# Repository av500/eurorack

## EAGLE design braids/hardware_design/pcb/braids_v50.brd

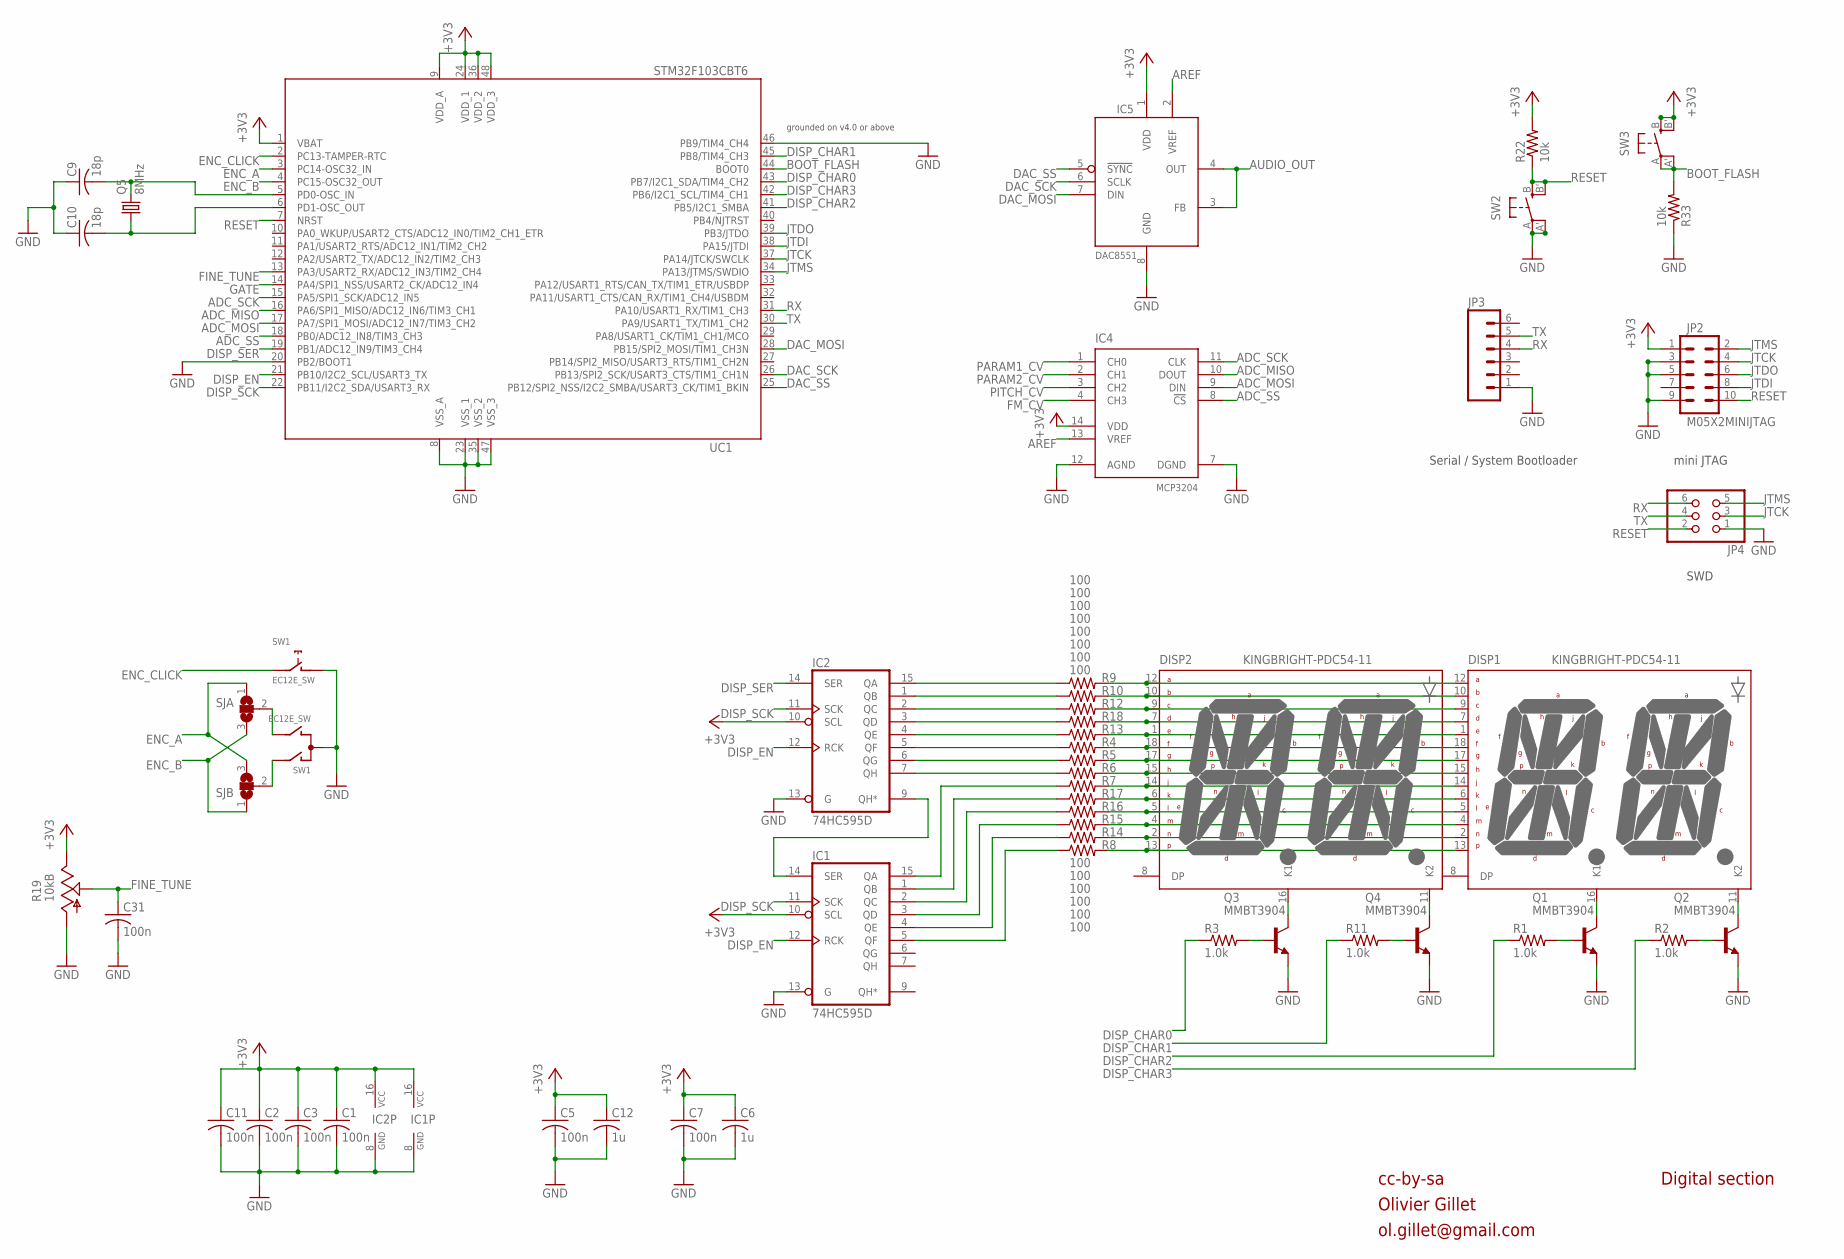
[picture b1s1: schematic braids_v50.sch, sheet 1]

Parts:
C1, C2, C3, C5, C7, C11, C31: 100n; C0603
C6, C12: 1u; C0603
C9, C10: 18p; C0603
DISP1, DISP2: KINGBRIGHT-PDC54-11; PDC54
IC1, IC2: 74HC595D; SO16
IC4: MCP3204; SO14
IC5: DAC8551; MSOP-8
JP2: M05X2MINIJTAG; 2X5-1.27
JP3: M06SIP; 1X06
JP4: PINHD-2X3"; 2X03
Q1, Q2, Q3, Q4: MMBT3904; SOT23-BEC
Q5: 8MHz; HC49UP
R1, R2, R3, R11: 1.0k; R0603
R4, R5, R6, R7, R8, R9, R10, R12, R13, R14, R15, R16, R17, R18: 100; R0603
R19: 10kB; ALPS_POT_VERTICAL_PS
R22, R33: 10k; R0603
SJA: SJ2W; SJ_2
SJB: SJ2W; SJ_2
SW1: EC12E_SW; ALPS_EC12E_SW
SW2, SW3: EVQQ2; EVQ-Q2
UC1: STM32F103CBT6; LQFP48

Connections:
+3V3: C1.1, C2.1, C3.1, C5.1, C6.1, C7.1, C11.1, C12.1, IC1.10 (SCL), IC1.16 (VCC), IC2.10 (SCL), IC2.16 (VCC), IC4.14 (VDD), IC5.1 (VDD), JP2.1, R19.P$1 (E), R22.2, SW3.B (S), SW3.B' (S1), UC1.1 (VBAT), UC1.9 (VDD_A), UC1.24 (VDD_1), UC1.36 (VDD_2), UC1.48 (VDD_3); also elsewhere on the board
ADC_MISO: IC4.10 (DOUT), UC1.16 (PA6/SPI1_MISO/ADC12_IN6/TIM3_CH1)
ADC_MOSI: IC4.9 (DIN), UC1.17 (PA7/SPI1_MOSI/ADC12_IN7/TIM3_CH2)
ADC_SCK: IC4.11 (CLK), UC1.15 (PA5/SPI1_SCK/ADC12_IN5)
ADC_SS: IC4.8 (!CS), UC1.18 (PB0/ADC12_IN8/TIM3_CH3)
AREF: IC4.13 (VREF), IC5.2 (VREF); also elsewhere on the board
AUDIO_OUT: IC5.3 (FB), IC5.4 (OUT); also elsewhere on the board
BOOT_FLASH: R33.2, SW3.A, SW3.A' (P1), UC1.44 (BOOT0)
DAC_MOSI: IC5.7 (DIN), UC1.28 (PB15/SPI2_MOSI/TIM1_CH3N)
DAC_SCK: IC5.6 (SCLK), UC1.26 (PB13/SPI2_SCK/USART3_CTS/TIM1_CH1N)
DAC_SS: IC5.5 (!SYNC), UC1.25 (PB12/SPI2_NSS/I2C2_SMBA/USART3_CK/TIM1_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)
DISP_CHAR0: R3.1, UC1.43 (PB7/I2C1_SDA/TIM4_CH2)
DISP_CHAR1: R11.1, UC1.45 (PB8/TIM4_CH3)
DISP_CHAR2: R1.1, UC1.41 (PB5/I2C1_SMBA)
DISP_CHAR3: R2.1, UC1.42 (PB6/I2C1_SCL/TIM4_CH1)
DISP_EN: IC1.12 (RCK), IC2.12 (RCK), UC1.21 (PB10/I2C2_SCL/USART3_TX)
DISP_SCK: IC1.11 (SCK), IC2.11 (SCK), UC1.22 (PB11/I2C2_SDA/USART3_RX)
DISP_SER: IC2.14 (SER), UC1.19 (PB1/ADC12_IN9/TIM3_CH4)
ENC_A: SJA.1, SJB.3, UC1.3 (PC14-OSC32_IN)
ENC_B: SJA.3, SJB.1, UC1.4 (PC15-OSC32_OUT)
ENC_CLICK: SW1.E (2), UC1.2 (PC13-TAMPER-RTC)
FINE_TUNE: C31.1, R19.P$2 (S), UC1.13 (PA3/USART2_RX/ADC12_IN3/TIM2_CH4)
FM_CV: IC4.4 (CH3); also elsewhere on the board
GATE: UC1.14 (PA4/SPI1_NSS/USART2_CK/ADC12_IN4); also elsewhere on the board
GND: C1.2, C2.2, C3.2, C5.2, C6.2, C7.2, C9.1, C10.1, C11.2, C12.2, C31.2, IC1.8 (GND), IC1.13 (G), IC2.8 (GND), IC2.13 (G), IC4.7 (DGND), IC4.12 (AGND), IC5.8 (GND), JP2.3, JP2.5, JP2.9, JP3.1, JP4.1, Q1.E, Q2.E, Q3.E, Q4.E, R19.P$3 (A), R33.1, SW1.C, SW1.D (1), SW2.A, SW2.A' (P1), UC1.8 (VSS_A), UC1.20 (PB2/BOOT1), UC1.23 (VSS_1), UC1.35 (VSS_2), UC1.46 (PB9/TIM4_CH4), UC1.47 (VSS_3); also elsewhere on the board
JTCK: JP2.4, JP4.3, UC1.37 (PA14/JTCK/SWCLK)
JTDI: JP2.8, UC1.38 (PA15/JTDI)
JTDO: JP2.6, UC1.39 (PB3/JTDO)
JTMS: JP2.2, JP4.5, UC1.34 (PA13/JTMS/SWDIO)
unnamed: DISP2.16 (K1), Q3.C
unnamed: DISP2.11 (K2), Q4.C
unnamed: DISP1.16 (K1), Q1.C
unnamed: DISP1.11 (K2), Q2.C
unnamed: Q3.B, R3.2
unnamed: Q4.B, R11.2
unnamed: C9.2, Q5.2, UC1.5 (PD0-OSC_IN)
unnamed: C10.2, Q5.1, UC1.6 (PD1-OSC_OUT)
unnamed: Q1.B, R1.2
unnamed: Q2.B, R2.2
unnamed: SJB.2, SW1.A
unnamed: DISP1.12 (A), DISP2.12 (A), R9.2
unnamed: DISP1.10 (B), DISP2.10 (B), R10.2
unnamed: DISP1.9 (C), DISP2.9 (C), R12.2
unnamed: DISP1.7 (D), DISP2.7 (D), R18.2
unnamed: DISP1.1 (E), DISP2.1 (E), R13.2
unnamed: DISP1.18 (F), DISP2.18 (F), R4.2
unnamed: DISP1.17 (G), DISP2.17 (G), R5.2
unnamed: DISP1.15 (H), DISP2.15 (H), R6.2
unnamed: DISP1.14 (J), DISP2.14 (J), R7.2
unnamed: DISP1.6 (K), DISP2.6 (K), R17.2
unnamed: DISP1.5 (L), DISP2.5 (L), R16.2
unnamed: DISP1.4 (M), DISP2.4 (M), R15.2
unnamed: DISP1.2 (N), DISP2.2 (N), R14.2
unnamed: DISP1.13, DISP2.13, R8.2
unnamed: IC2.7 (QH), R6.1
unnamed: IC1.14 (SER), IC2.9 (QH*)
unnamed: IC2.15 (QA), R9.1
unnamed: IC2.1 (QB), R10.1
unnamed: IC2.2 (QC), R12.1
unnamed: IC2.3 (QD), R18.1
unnamed: IC2.4 (QE), R13.1
unnamed: IC2.5 (QF), R4.1
unnamed: IC2.6 (QG), R5.1
unnamed: IC1.15 (QA), R7.1
unnamed: IC1.1 (QB), R17.1
unnamed: IC1.2 (QC), R16.1
unnamed: IC1.3 (QD), R15.1
unnamed: IC1.4 (QE), R14.1
unnamed: IC1.5 (QF), R8.1
unnamed: SJA.2, SW1.B
PARAM1_CV: IC4.1 (CH0); also elsewhere on the board
PARAM2_CV: IC4.2 (CH1); also elsewhere on the board
PITCH_CV: IC4.3 (CH2); also elsewhere on the board
RESET: JP2.10, JP4.2, R22.1, SW2.B (S), SW2.B' (S1), UC1.7 (NRST)
RX: JP3.4, JP4.6, UC1.31 (PA10/USART1_RX/TIM1_CH3)
TX: JP3.5, JP4.4, UC1.30 (PA9/USART1_TX/TIM1_CH2)

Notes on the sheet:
cc-by-sa
Olivier Gillet
ol.gillet@gmail.com
Serial / System Bootloader
mini JTAG
Digital section
grounded on v4.0 or above
SWD

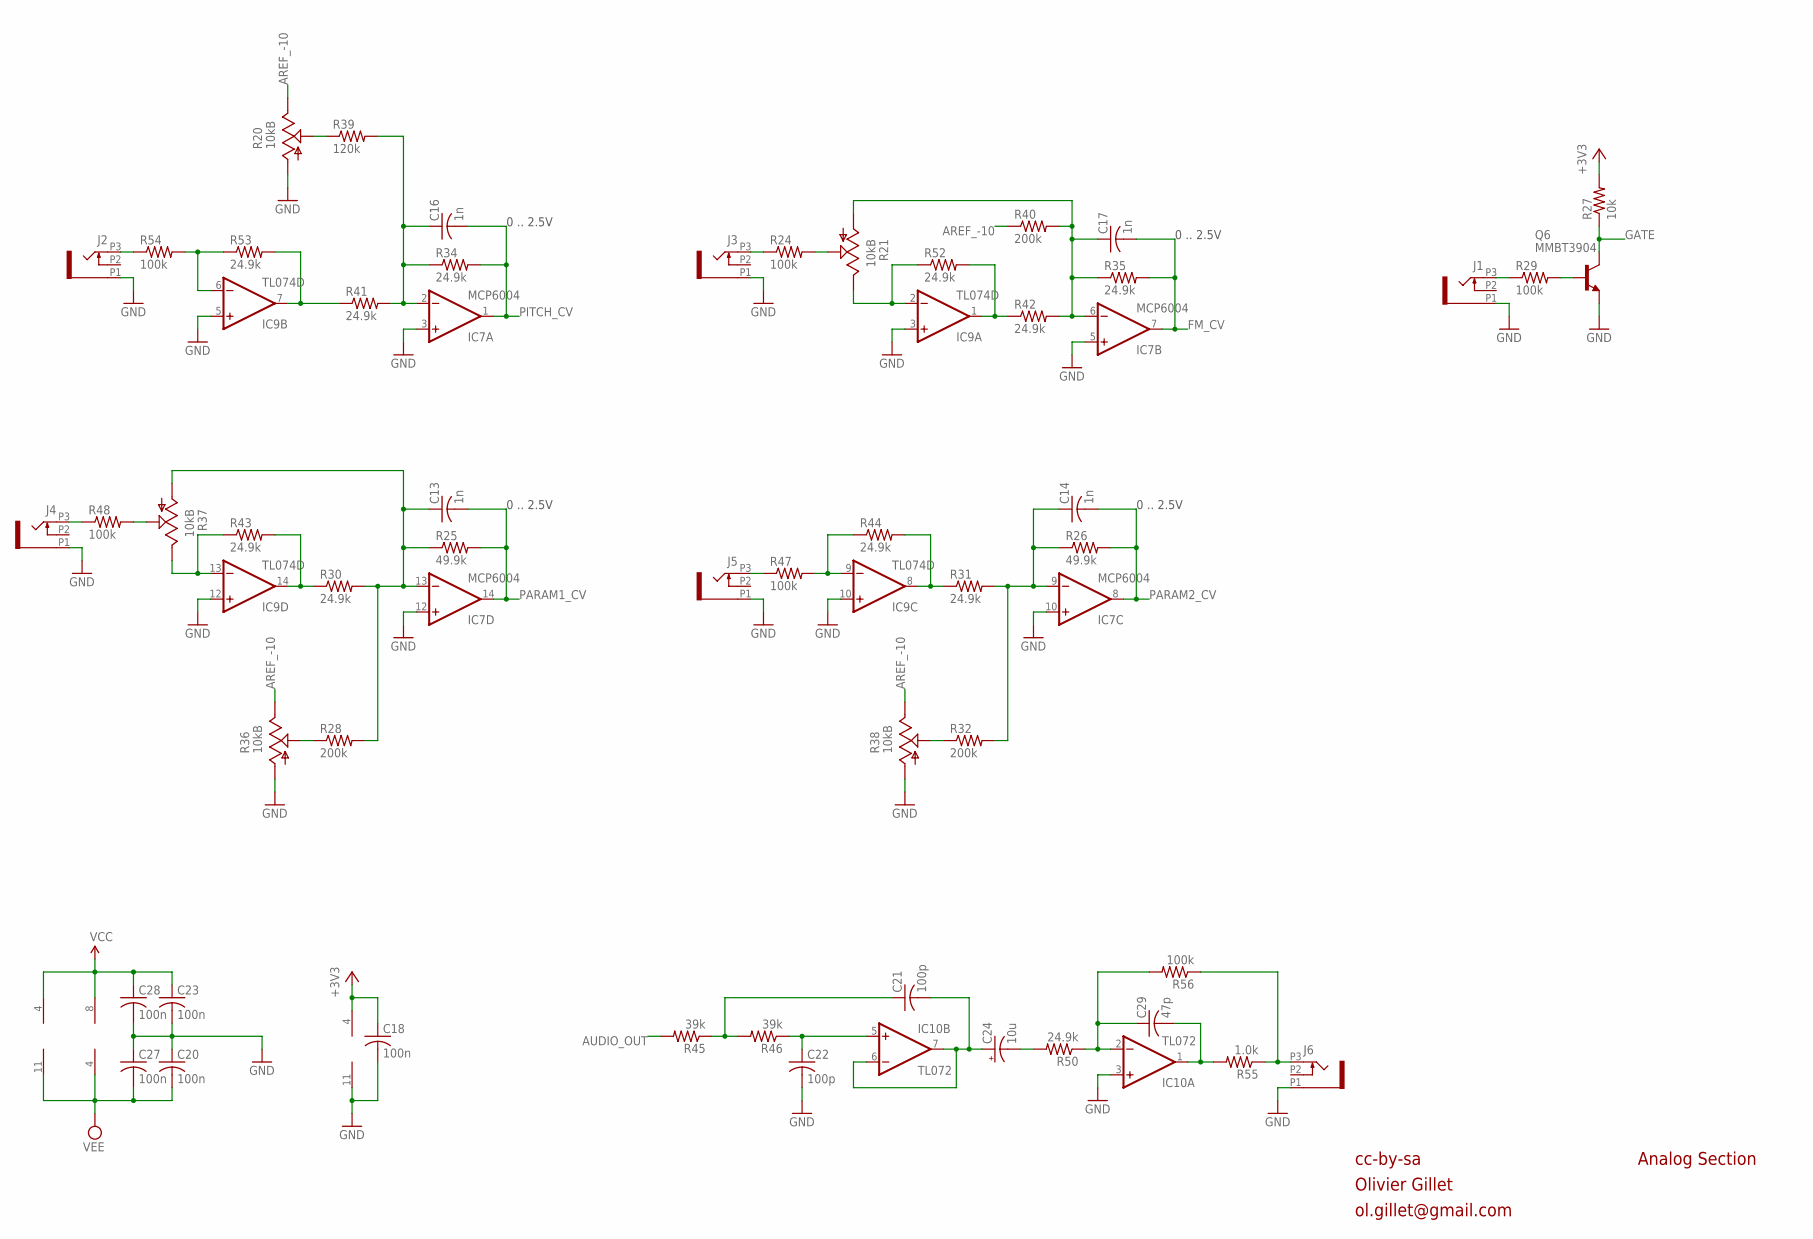
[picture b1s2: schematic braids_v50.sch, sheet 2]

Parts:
C13, C14, C16, C17: 1n; C0603
C18, C20, C23, C27, C28: 100n; C0603
C21, C22: 100p; C0603
C24: 10u; PANASONIC_B
C29: 47p; C0603
IC7: MCP6004; SO14
IC9: TL074D; SO14
IC10: TL072; SO08
J1, J2, J3, J4, J5, J6: PJ301_THONKICONN6; WQP_PJ_301M6
Q6: MMBT3904; SOT23-BEC
R20, R21, R36, R37, R38: 10kB; ALPS_POT_VERTICAL_PS
R24, R29, R47, R48, R54, R56: 100k; R0603
R25, R26: 49.9k; R0603
R27: 10k; R0603
R28, R32, R40: 200k; R0603
R30, R31, R34, R35, R41, R42, R43, R44, R50, R52, R53: 24.9k; R0603
R39: 120k; R0603
R45, R46: 39k; R0603
R55: 1.0k; R0603

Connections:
+3V3: C18.1, IC7.4 (V+), R27.2; also elsewhere on the board
AREF_-10: R20.P$1 (E), R36.P$1 (E), R38.P$1 (E), R40.1; also elsewhere on the board
AUDIO_OUT: R45.2; also elsewhere on the board
FM_CV: C17.2, IC7.7 (OUT), R35.2; also elsewhere on the board
GATE: Q6.C, R27.1; also elsewhere on the board
GND: C18.2, C20.1, C22.2, C23.2, C27.1, C28.2, IC7.3 (+IN), IC7.5 (+IN), IC7.10 (+IN), IC7.11 (V-), IC7.12 (+IN), IC9.3 (+IN), IC9.5 (+IN), IC9.10 (+IN), IC9.12 (+IN), IC10.3 (+IN), J1.P1 (1), J2.P1 (1), J3.P1 (1), J4.P1 (1), J5.P1 (1), J6.P1 (1), Q6.E, R20.P$3 (A), R36.P$3 (A), R38.P$3 (A); also elsewhere on the board
unnamed: IC9.7 (OUT), R41.1, R53.2
unnamed: R20.P$2 (S), R39.1
unnamed: J2.P3 (3), R54.1
unnamed: C16.1, IC7.2 (-IN), R34.1, R39.2, R41.2
unnamed: IC9.6 (-IN), R53.1, R54.2
unnamed: J3.P3 (3), R24.1
unnamed: J4.P3 (3), R48.1
unnamed: R21.P$2 (S), R24.2
unnamed: IC9.13 (-IN), R37.P$1 (E), R43.1
unnamed: IC9.14 (OUT), R30.1, R43.2
unnamed: IC9.2 (-IN), R21.P$1 (E), R52.1
unnamed: IC9.1 (OUT), R42.1, R52.2
unnamed: C17.1, IC7.6 (-IN), R21.P$3 (A), R35.1, R40.2, R42.2
unnamed: J1.P3 (3), R29.1
unnamed: IC9.8 (OUT), R31.1, R44.2
unnamed: C13.1, IC7.13 (-IN), R25.1, R28.2, R30.2, R37.P$3 (A)
unnamed: J5.P3 (3), R47.1
unnamed: R28.1, R36.P$2 (S)
unnamed: R37.P$2 (S), R48.2
unnamed: IC9.9 (-IN), R44.1, R47.2
unnamed: R32.1, R38.P$2 (S)
unnamed: Q6.B, R29.2
unnamed: C21.2, C24.+, IC10.6 (-IN), IC10.7 (OUT)
unnamed: C24.-, R50.2
unnamed: C22.1, IC10.5 (+IN), R46.1
unnamed: C14.1, IC7.9 (-IN), R26.1, R31.2, R32.2
unnamed: C21.1, R45.1, R46.2
unnamed: J6.P3 (3), R55.1, R56.1
unnamed: C29.2, IC10.1 (OUT), R55.2
unnamed: C29.1, IC10.2 (-IN), R50.1, R56.2
PARAM1_CV: C13.2, IC7.14 (OUT), R25.2; also elsewhere on the board
PARAM2_CV: C14.2, IC7.8 (OUT), R26.2; also elsewhere on the board
PITCH_CV: C16.2, IC7.1 (OUT), R34.2; also elsewhere on the board
VCC: C23.1, C28.1, IC9.4 (V+), IC10.8 (V+); also elsewhere on the board
VEE: C20.2, C27.2, IC9.11 (V-), IC10.4 (V-); also elsewhere on the board

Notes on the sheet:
cc-by-sa
Olivier Gillet
ol.gillet@gmail.com
Analog Section
0 .. 2.5V

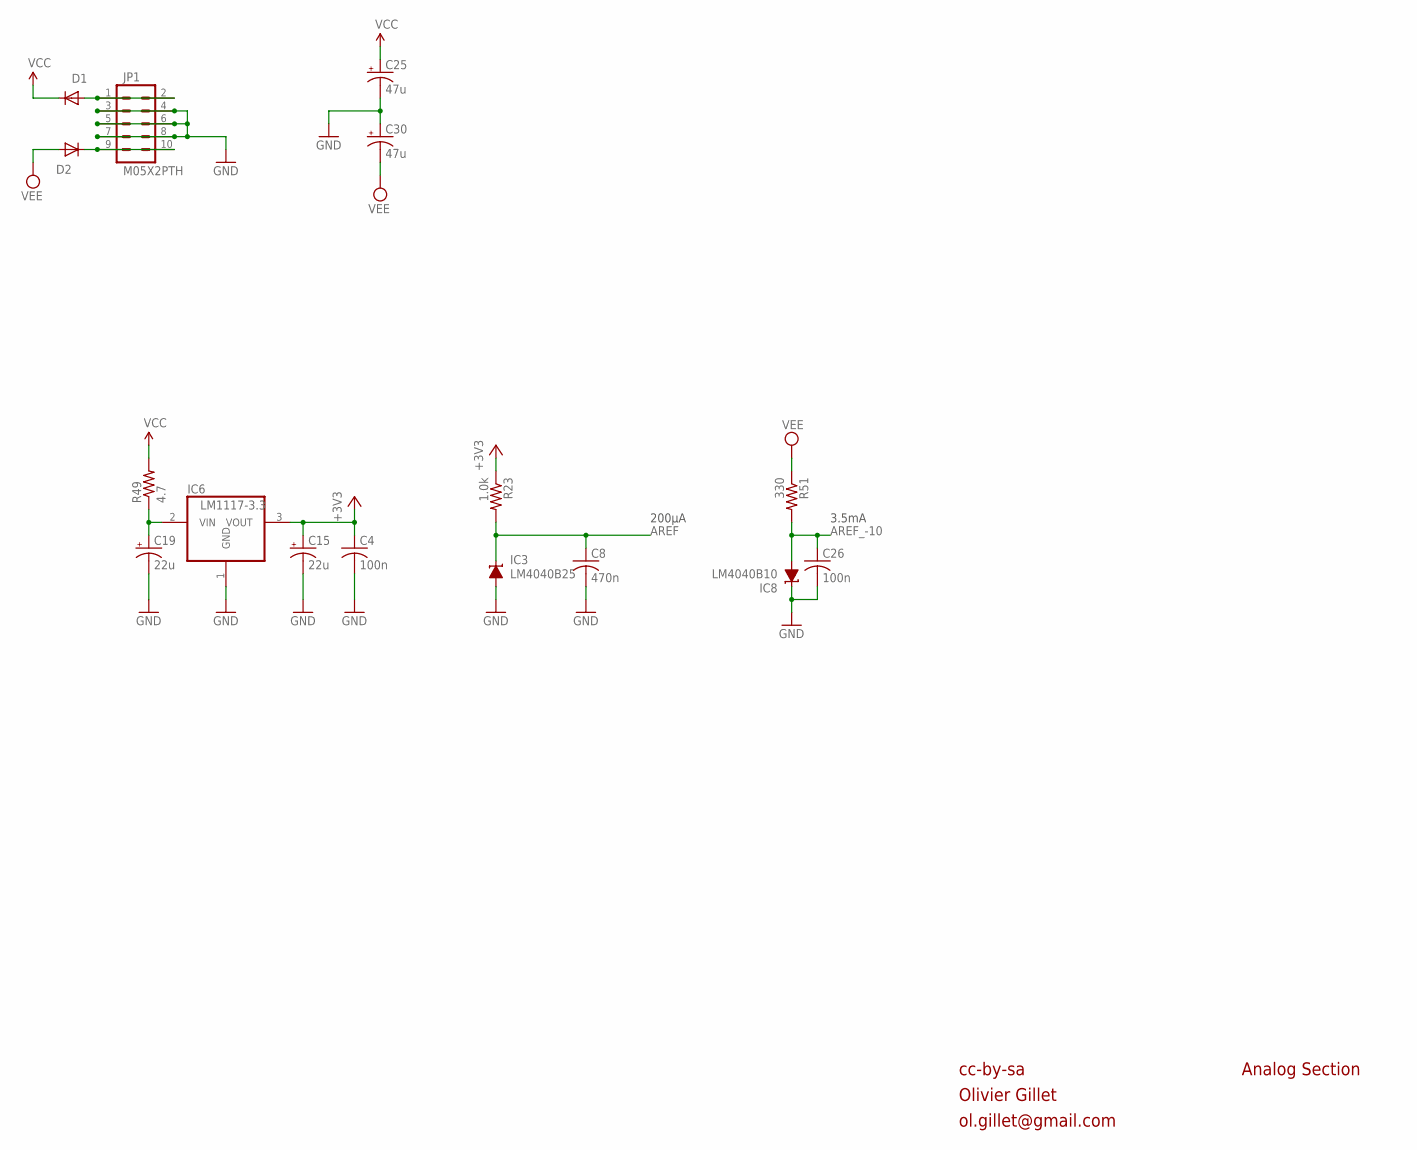
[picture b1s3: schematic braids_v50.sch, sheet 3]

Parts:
C4, C26: 100n; C0603
C8: 470n; C0603
C15, C19: 22u; PANASONIC_C
C25, C30: 47u; PANASONIC_D
D1, D2: 1N5819HW; SOD123
IC3: LM4040B25; DBZ_R-PDSO-G3
IC6: LM1117-3.3; TO252
IC8: LM4040B10; DBZ_R-PDSO-G3
JP1: M05X2PTH; AVR_ICSP
R23: 1.0k; R0603
R49: 4.7; R1206
R51: 330; R0603

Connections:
+3V3: C4.1, C15.+, IC6.3 (VOUT), R23.1; also elsewhere on the board
AREF: C8.1, IC3.1 (C), R23.2; also elsewhere on the board
AREF_-10: C26.1, IC8.2 (A), R51.2; also elsewhere on the board
GND: C4.2, C8.2, C15.-, C19.-, C25.-, C26.2, C30.+, IC3.2 (A), IC6.1 (GND), IC8.1 (C), JP1.3, JP1.4, JP1.5, JP1.6, JP1.7, JP1.8; also elsewhere on the board
unnamed: C19.+, IC6.2 (VIN), R49.1
unnamed: D1.A, JP1.1, JP1.2
unnamed: D2.C, JP1.9, JP1.10
VCC: C25.+, D1.C, R49.2; also elsewhere on the board
VEE: C30.-, D2.A, R51.1; also elsewhere on the board

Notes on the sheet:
3.5mA
200µA
cc-by-sa
Olivier Gillet
ol.gillet@gmail.com
Analog Section

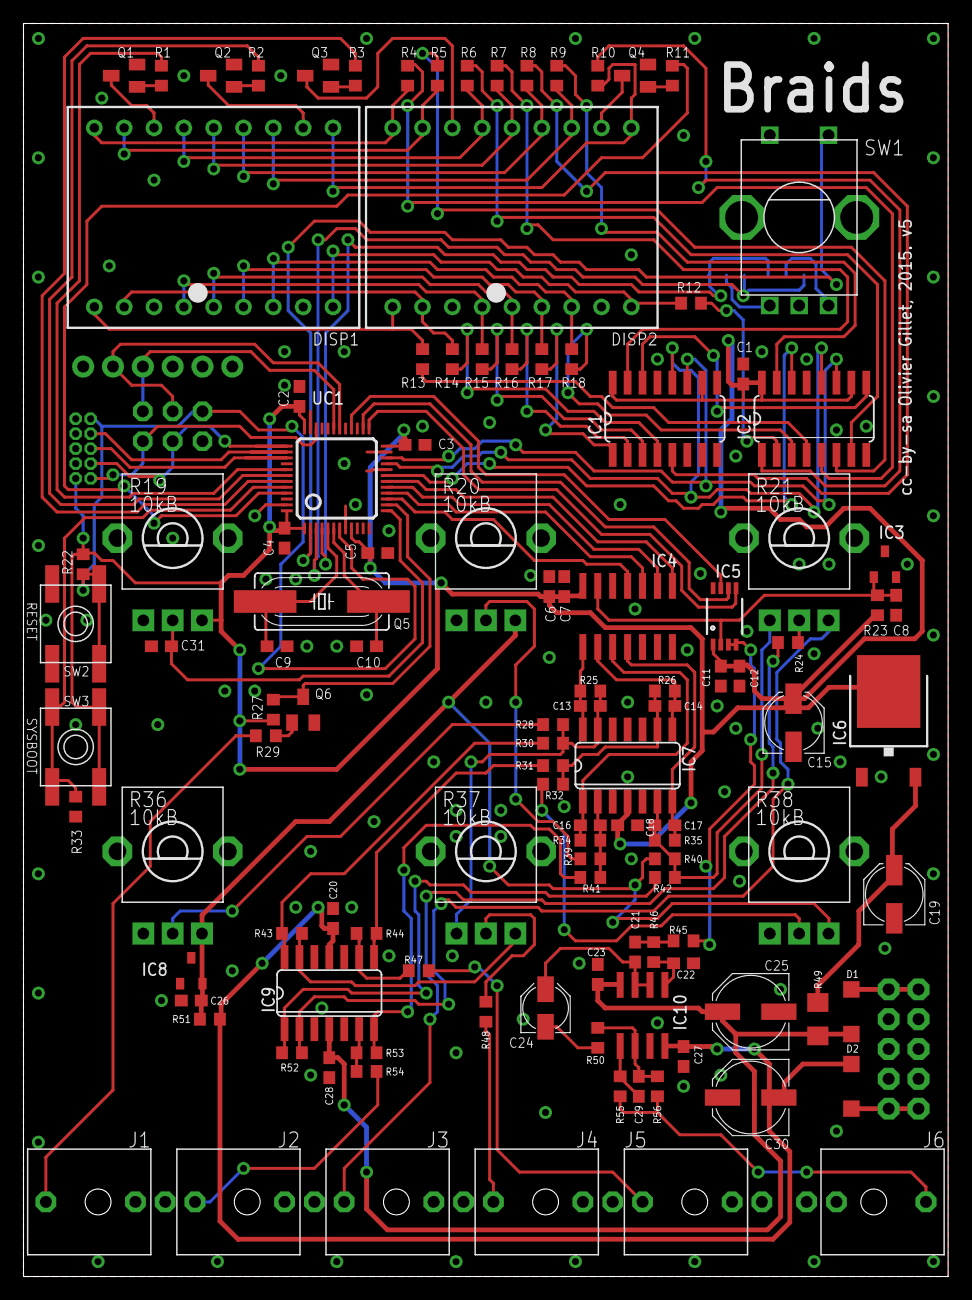
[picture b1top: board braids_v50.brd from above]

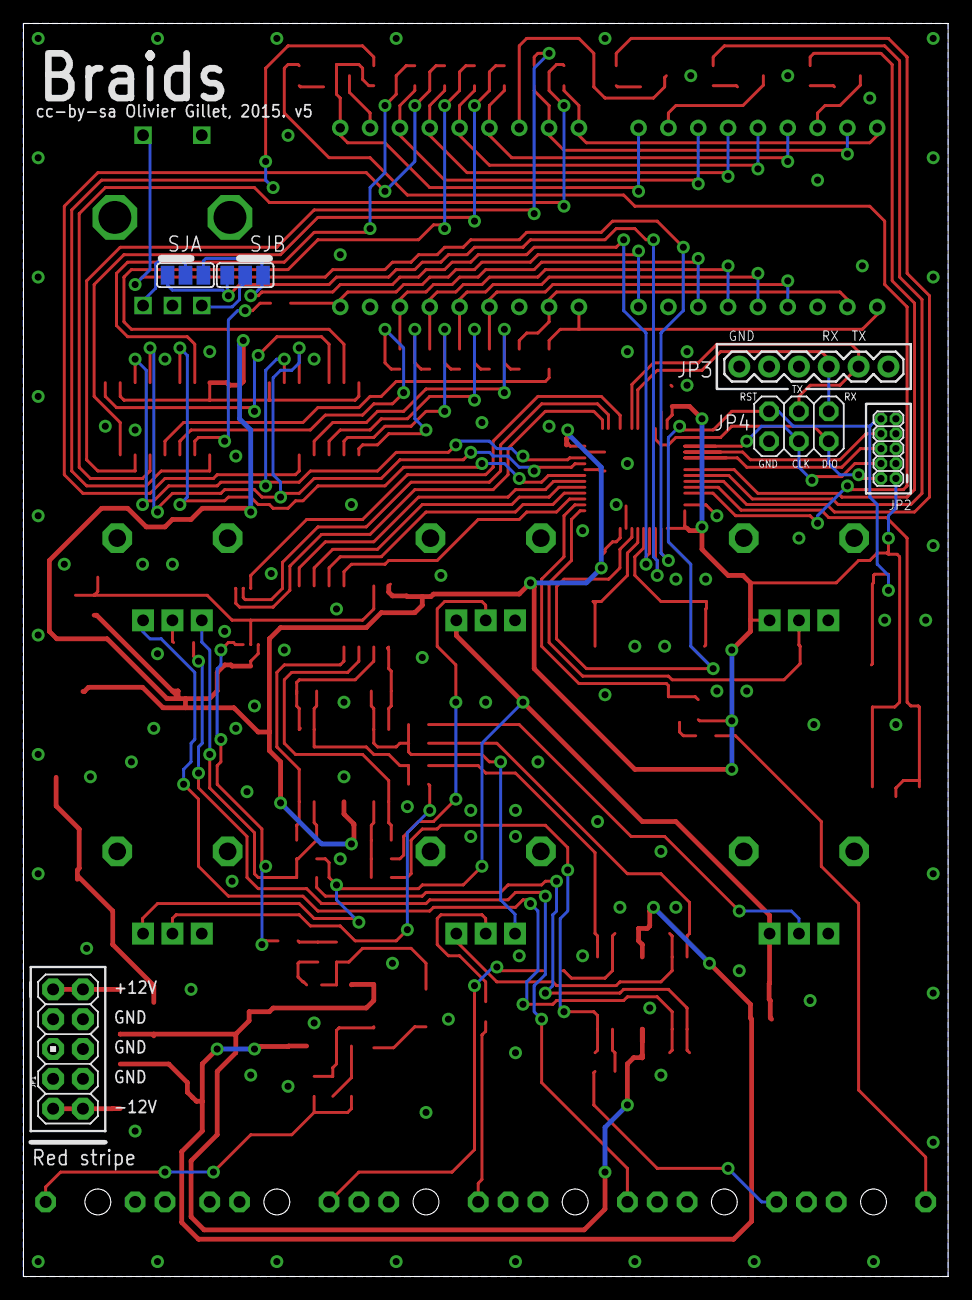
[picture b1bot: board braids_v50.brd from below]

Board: 2 copper layers, 78.7 x 106.7 mm, 123 parts (6 on the bottom side), 112 nets.

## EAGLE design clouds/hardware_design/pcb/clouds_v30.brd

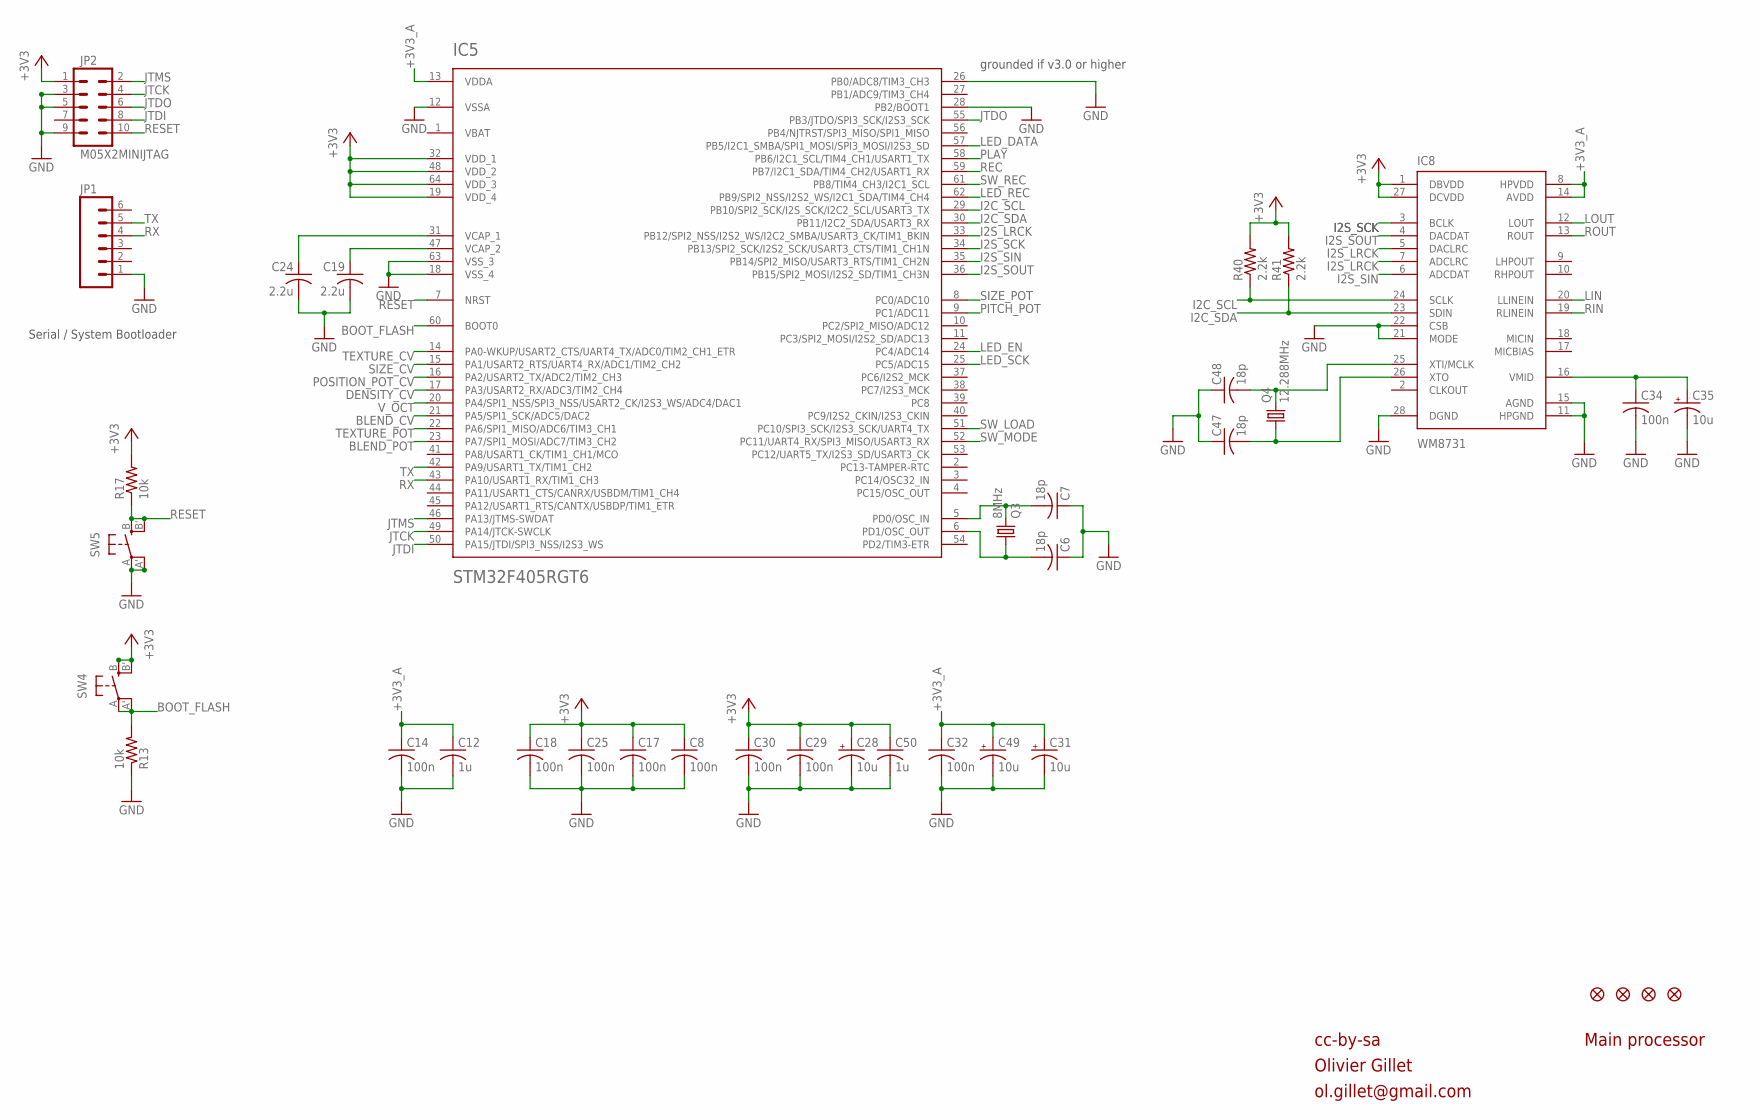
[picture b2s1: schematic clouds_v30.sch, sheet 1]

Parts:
C6, C7, C47, C48: 18p; C0603
C8, C14, C17, C18, C25, C29, C30, C32, C34: 100n; C0603
C12, C50: 1u; C0603
C19, C24: 2.2u; C0805
C28, C49: 10u; PANASONIC_A
C31, C35: 10u; PANASONIC_B
F1, F2, F3, F4: FIDUCIAL1X2; FIDUCIAL-1X2
IC5: STM32F405RGT6; TQFP-10X10-64
IC8: WM8731; SSOP28
JP1: M06SIP; 1X06
JP2: M05X2MINIJTAG; 2X5-1.27
Q3: 8MHz; HC49UP
Q4: 12.288MHz; HC49UP
R13, R17: 10k; R0603
R40, R41: 2.2k; R0603
SW4, SW5: EVQQ2; EVQ-Q2

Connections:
+3V3: C8.1, C17.1, C18.1, C25.1, C28.+, C29.1, C30.1, C50.1, IC5.19 (VDD_4), IC5.32 (VDD_1), IC5.48 (VDD_2), IC5.64 (VDD_3), IC8.1 (DBVDD), IC8.27 (DCVDD), JP2.1, R17.2, R40.2, R41.2, SW4.B (S), SW4.B' (S1); also elsewhere on the board
+3V3_A: C12.1, C14.1, C31.+, C32.1, C49.+, IC5.13 (VDDA), IC8.8 (HPVDD), IC8.14 (AVDD); also elsewhere on the board
BLEND_CV: IC5.21 (PA5/SPI1_SCK/ADC5/DAC2); also elsewhere on the board
BLEND_POT: IC5.23 (PA7/SPI1_MOSI/ADC7/TIM3_CH2); also elsewhere on the board
BOOT_FLASH: IC5.60 (BOOT0), R13.2, SW4.A, SW4.A' (P1)
DENSITY_CV: IC5.17 (PA3/USART2_RX/ADC3/TIM2_CH4); also elsewhere on the board
GND: C6.1, C7.1, C8.2, C12.2, C14.2, C17.2, C18.2, C19.2, C24.2, C25.2, C28.-, C29.2, C30.2, C31.-, C32.2, C34.2, C35.-, C47.1, C48.1, C49.-, C50.2, IC5.12 (VSSA), IC5.18 (VSS_4), IC5.26 (PB0/ADC8/TIM3_CH3), IC5.28 (PB2/BOOT1), IC5.63 (VSS_3), IC8.11 (HPGND), IC8.15 (AGND), IC8.21 (MODE), IC8.22 (CSB), IC8.28 (DGND), JP1.1, JP2.3, JP2.5, JP2.9, R13.1, SW5.A, SW5.A' (P1); also elsewhere on the board
I2C_SCL: IC5.29 (PB10/SPI2_SCK/I2S_SCK/I2C2_SCL/USART3_TX), IC8.24 (SCLK), R40.1
I2C_SDA: IC5.30 (PB11/I2C2_SDA/USART3_RX), IC8.23 (SDIN), R41.1
I2S_LRCK: IC5.33 (PB12/SPI2_NSS/I2S2_WS/I2C2_SMBA/USART3_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), IC8.5 (DACLRC), IC8.7 (ADCLRC)
I2S_SCK: IC5.34 (PB13/SPI2_SCK/I2S2_SCK/USART3_CTS/TIM1_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), IC8.3 (BCLK)
I2S_SIN: IC5.35 (PB14/SPI2_MISO/USART3_RTS/TIM1_CH2N), IC8.6 (ADCDAT)
I2S_SOUT: IC5.36 (PB15/SPI2_MOSI/I2S2_SD/TIM1_CH3N), IC8.4 (DACDAT)
JTCK: IC5.49 (PA14/JTCK-SWCLK), JP2.4
JTDI: IC5.50 (PA15/JTDI/SPI3_NSS/I2S3_WS), JP2.8
JTDO: IC5.55 (PB3/JTDO/SPI3_SCK/I2S3_SCK), JP2.6
JTMS: IC5.46 (PA13/JTMS-SWDAT), JP2.2
LED_DATA: IC5.57 (PB5/I2C1_SMBA/SPI1_MOSI/SPI3_MOSI/I2S3_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); also elsewhere on the board
LED_EN: IC5.24 (PC4/ADC14); also elsewhere on the board
LED_REC: IC5.62 (PB9/SPI2_NSS/I2S2_WS/I2C1_SDA/TIM4_CH4); also elsewhere on the board
LED_SCK: IC5.25 (PC5/ADC15); also elsewhere on the board
LIN: IC8.20 (LLINEIN); also elsewhere on the board
LOUT: IC8.12 (LOUT); also elsewhere on the board
unnamed: C7.2, IC5.5 (PD0/OSC_IN), Q3.2
unnamed: C6.2, IC5.6 (PD1/OSC_OUT), Q3.1
unnamed: C19.1, IC5.47 (VCAP_2)
unnamed: C34.1, C35.+, IC8.16 (VMID)
unnamed: C24.1, IC5.31 (VCAP_1)
unnamed: C47.2, IC8.26 (XTO), Q4.1
unnamed: C48.2, IC8.25 (XTI/MCLK), Q4.2
PITCH_POT: IC5.9 (PC1/ADC11); also elsewhere on the board
PLAY: IC5.58 (PB6/I2C1_SCL/TIM4_CH1/USART1_TX); also elsewhere on the board
POSITION_POT_CV: IC5.16 (PA2/USART2_TX/ADC2/TIM2_CH3); also elsewhere on the board
REC: IC5.59 (PB7/I2C1_SDA/TIM4_CH2/USART1_RX); also elsewhere on the board
RESET: IC5.7 (NRST), JP2.10, R17.1, SW5.B (S), SW5.B' (S1)
RIN: IC8.19 (RLINEIN); also elsewhere on the board
ROUT: IC8.13 (ROUT); also elsewhere on the board
RX: IC5.43 (PA10/USART1_RX/TIM1_CH3), JP1.4
SIZE_CV: IC5.15 (PA1/USART2_RTS/UART4_RX/ADC1/TIM2_CH2); also elsewhere on the board
SIZE_POT: IC5.8 (PC0/ADC10); also elsewhere on the board
SW_LOAD: IC5.51 (PC10/SPI3_SCK/I2S3_SCK/UART4_TX); also elsewhere on the board
SW_MODE: IC5.52 (PC11/UART4_RX/SPI3_MISO/USART3_RX); also elsewhere on the board
SW_REC: IC5.61 (PB8/TIM4_CH3/I2C1_SCL); also elsewhere on the board
TEXTURE_CV: IC5.14 (PA0-WKUP/USART2_CTS/UART4_TX/ADC0/TIM2_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); also elsewhere on the board
TEXTURE_POT: IC5.22 (PA6/SPI1_MISO/ADC6/TIM3_CH1); also elsewhere on the board
TX: IC5.42 (PA9/USART1_TX/TIM1_CH2), JP1.5
VBAT: IC5.1 (VBAT)
V_OCT: IC5.20 (PA4/SPI1_NSS/SPI3_NSS/USART2_CK/I2S3_WS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); also elsewhere on the board

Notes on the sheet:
cc-by-sa
Olivier Gillet
ol.gillet@gmail.com
Main processor
Serial / System Bootloader
grounded if v3.0 or higher

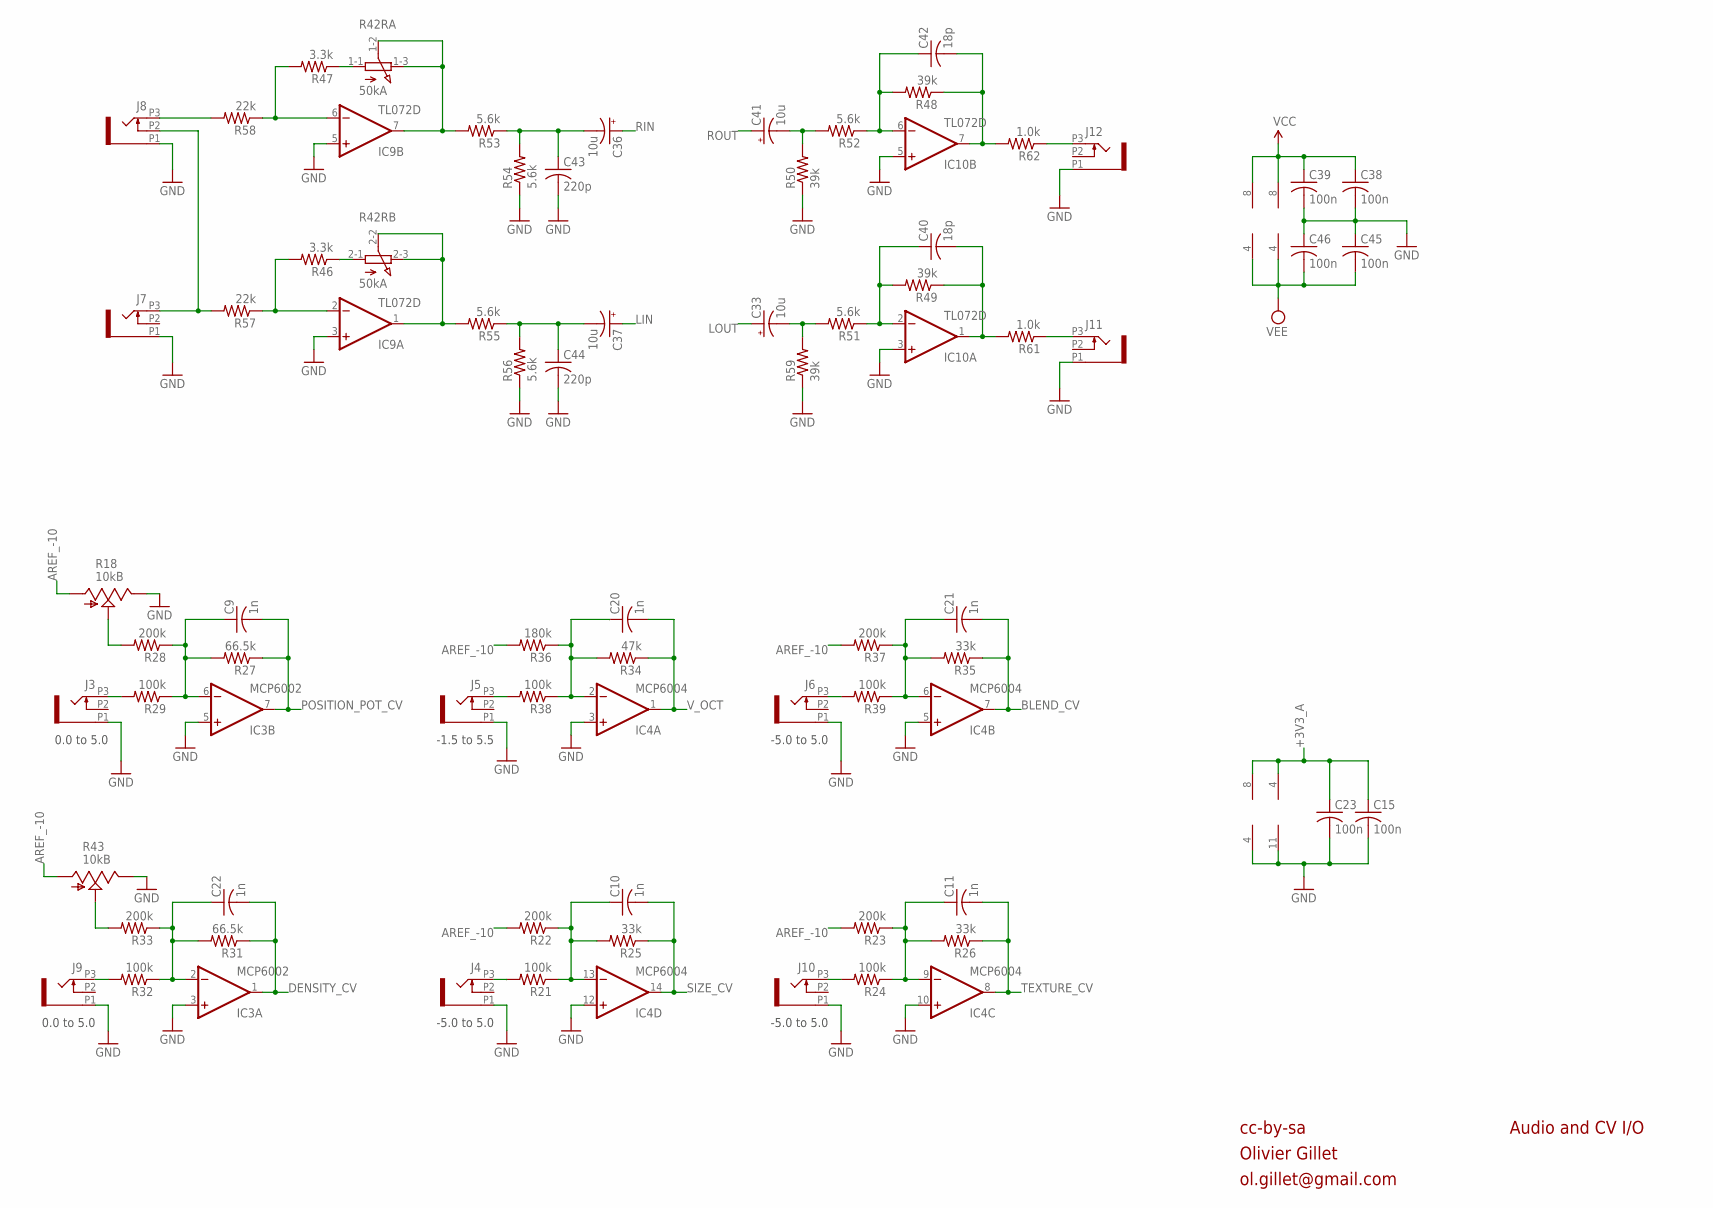
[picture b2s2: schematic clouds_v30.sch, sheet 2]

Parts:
C9, C10, C11, C20, C21, C22: 1n; C0603
C15, C23, C38, C39, C45, C46: 100n; C0603
C33, C36, C37, C41: 10u; PANASONIC_B
C40, C42: 18p; C0603
C43, C44: 220p; C0603
IC3: MCP6002; SO08
IC4: MCP6004; SO14
IC9, IC10: TL072D; SO08
J3, J4, J5, J6, J7, J8, J9, J10, J11, J12: PJ301_THONKICONN6; WQP_PJ_301M6
R18, R43: 10kB; ALPS_POT_VERTICAL_PS
R21, R24, R29, R32, R38, R39: 100k; R0603
R22, R23, R28, R33, R37: 200k; R0603
R25, R26, R35: 33k; R0603
R27, R31: 66.5k; R0603
R34: 47k; R0603
R36: 180k; R0603
R42: 50kA; ALPHA_RD902F-040
R46, R47: 3.3k; R0603
R48, R49, R50, R59: 39k; R0603
R51, R52, R53, R54, R55, R56: 5.6k; R0603
R57, R58: 22k; R0603
R61, R62: 1.0k; R0603

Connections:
+3V3_A: C15.1, C23.1, IC3.8 (V+), IC4.4 (V+); also elsewhere on the board
AREF_-10: R18.P$3 (A), R22.2, R23.2, R36.2, R37.2, R43.P$3 (A); also elsewhere on the board
BLEND_CV: C21.2, IC4.7 (OUT), R35.1; also elsewhere on the board
DENSITY_CV: C22.2, IC3.1 (OUT), R31.1; also elsewhere on the board
GND: C15.2, C23.2, C38.2, C39.2, C43.2, C44.2, C45.1, C46.1, IC3.3 (+IN), IC3.4 (V-), IC3.5 (+IN), IC4.3 (+IN), IC4.5 (+IN), IC4.10 (+IN), IC4.11 (V-), IC4.12 (+IN), IC9.3 (+IN), IC9.5 (+IN), IC10.3 (+IN), IC10.5 (+IN), J3.P1 (1), J4.P1 (1), J5.P1 (1), J6.P1 (1), J7.P1 (1), J8.P1 (1), J9.P1 (1), J10.P1 (1), J11.P1 (1), J12.P1 (1), R18.P$1 (E), R43.P$1 (E), R50.1, R54.1, R56.1, R59.1; also elsewhere on the board
LIN: C37.+; also elsewhere on the board
LOUT: C33.+; also elsewhere on the board
LOUT_JACK: J11.P3 (3), R61.1
unnamed: J4.P3 (3), R21.2
unnamed: C10.1, IC4.13 (-IN), R21.1, R22.1, R25.2
unnamed: J10.P3 (3), R24.2
unnamed: C11.1, IC4.9 (-IN), R23.1, R24.1, R26.2
unnamed: J6.P3 (3), R39.2
unnamed: J5.P3 (3), R38.2
unnamed: C20.1, IC4.2 (-IN), R34.2, R36.1, R38.1
unnamed: J9.P3 (3), R32.2
unnamed: C21.1, IC4.6 (-IN), R35.2, R37.1, R39.1
unnamed: C37.-, C44.1, R55.1, R56.2
unnamed: J8.P3 (3), R58.2
unnamed: J7.P3 (3), J8.P2 (2), R57.2
unnamed: C36.-, C43.1, R53.1, R54.2
unnamed: C41.-, R50.2, R52.2
unnamed: C22.1, IC3.2 (-IN), R31.2, R32.1, R33.1
unnamed: C42.1, IC10.6 (-IN), R48.2, R52.1
unnamed: R33.2, R43.P$2 (S)
unnamed: J3.P3 (3), R29.2
unnamed: C42.2, IC10.7 (OUT), R48.1, R62.2
unnamed: C9.1, IC3.6 (-IN), R27.2, R28.1, R29.1
unnamed: C33.-, R51.2, R59.2
unnamed: C40.1, IC10.2 (-IN), R49.2, R51.1
unnamed: C40.2, IC10.1 (OUT), R49.1, R61.2
unnamed: R18.P$2 (S), R28.2
unnamed: IC9.7 (OUT), R42.1-2 (S), R42.1-3 (E), R53.2
unnamed: IC9.1 (OUT), R42.2-2 (S), R42.2-3 (E), R55.2
unnamed: R42.1-1 (A), R47.1
unnamed: R42.2-1 (A), R46.1
unnamed: IC9.6 (-IN), R47.2, R58.1
unnamed: IC9.2 (-IN), R46.2, R57.1
POSITION_POT_CV: C9.2, IC3.7 (OUT), R27.1; also elsewhere on the board
RIN: C36.+; also elsewhere on the board
ROUT: C41.+; also elsewhere on the board
ROUT_JACK: J12.P3 (3), R62.1
SIZE_CV: C10.2, IC4.14 (OUT), R25.1; also elsewhere on the board
TEXTURE_CV: C11.2, IC4.8 (OUT), R26.1; also elsewhere on the board
VCC: C38.1, C39.1, IC9.8 (V+), IC10.8 (V+); also elsewhere on the board
VEE: C45.2, C46.2, IC9.4 (V-), IC10.4 (V-); also elsewhere on the board
V_OCT: C20.2, IC4.1 (OUT), R34.1; also elsewhere on the board

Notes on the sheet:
cc-by-sa
Olivier Gillet
ol.gillet@gmail.com
Audio and CV I/O
0.0 to 5.0
-1.5 to 5.5
-5.0 to 5.0

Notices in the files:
braids/hardware_design/pcb/braids_v50.brd:
cc-by-sa Olivier Gillet, 2015. v5
clouds/hardware_design/pcb/clouds_v30.brd:
cc-by-sa Olivier Gillet, 2015. v3
